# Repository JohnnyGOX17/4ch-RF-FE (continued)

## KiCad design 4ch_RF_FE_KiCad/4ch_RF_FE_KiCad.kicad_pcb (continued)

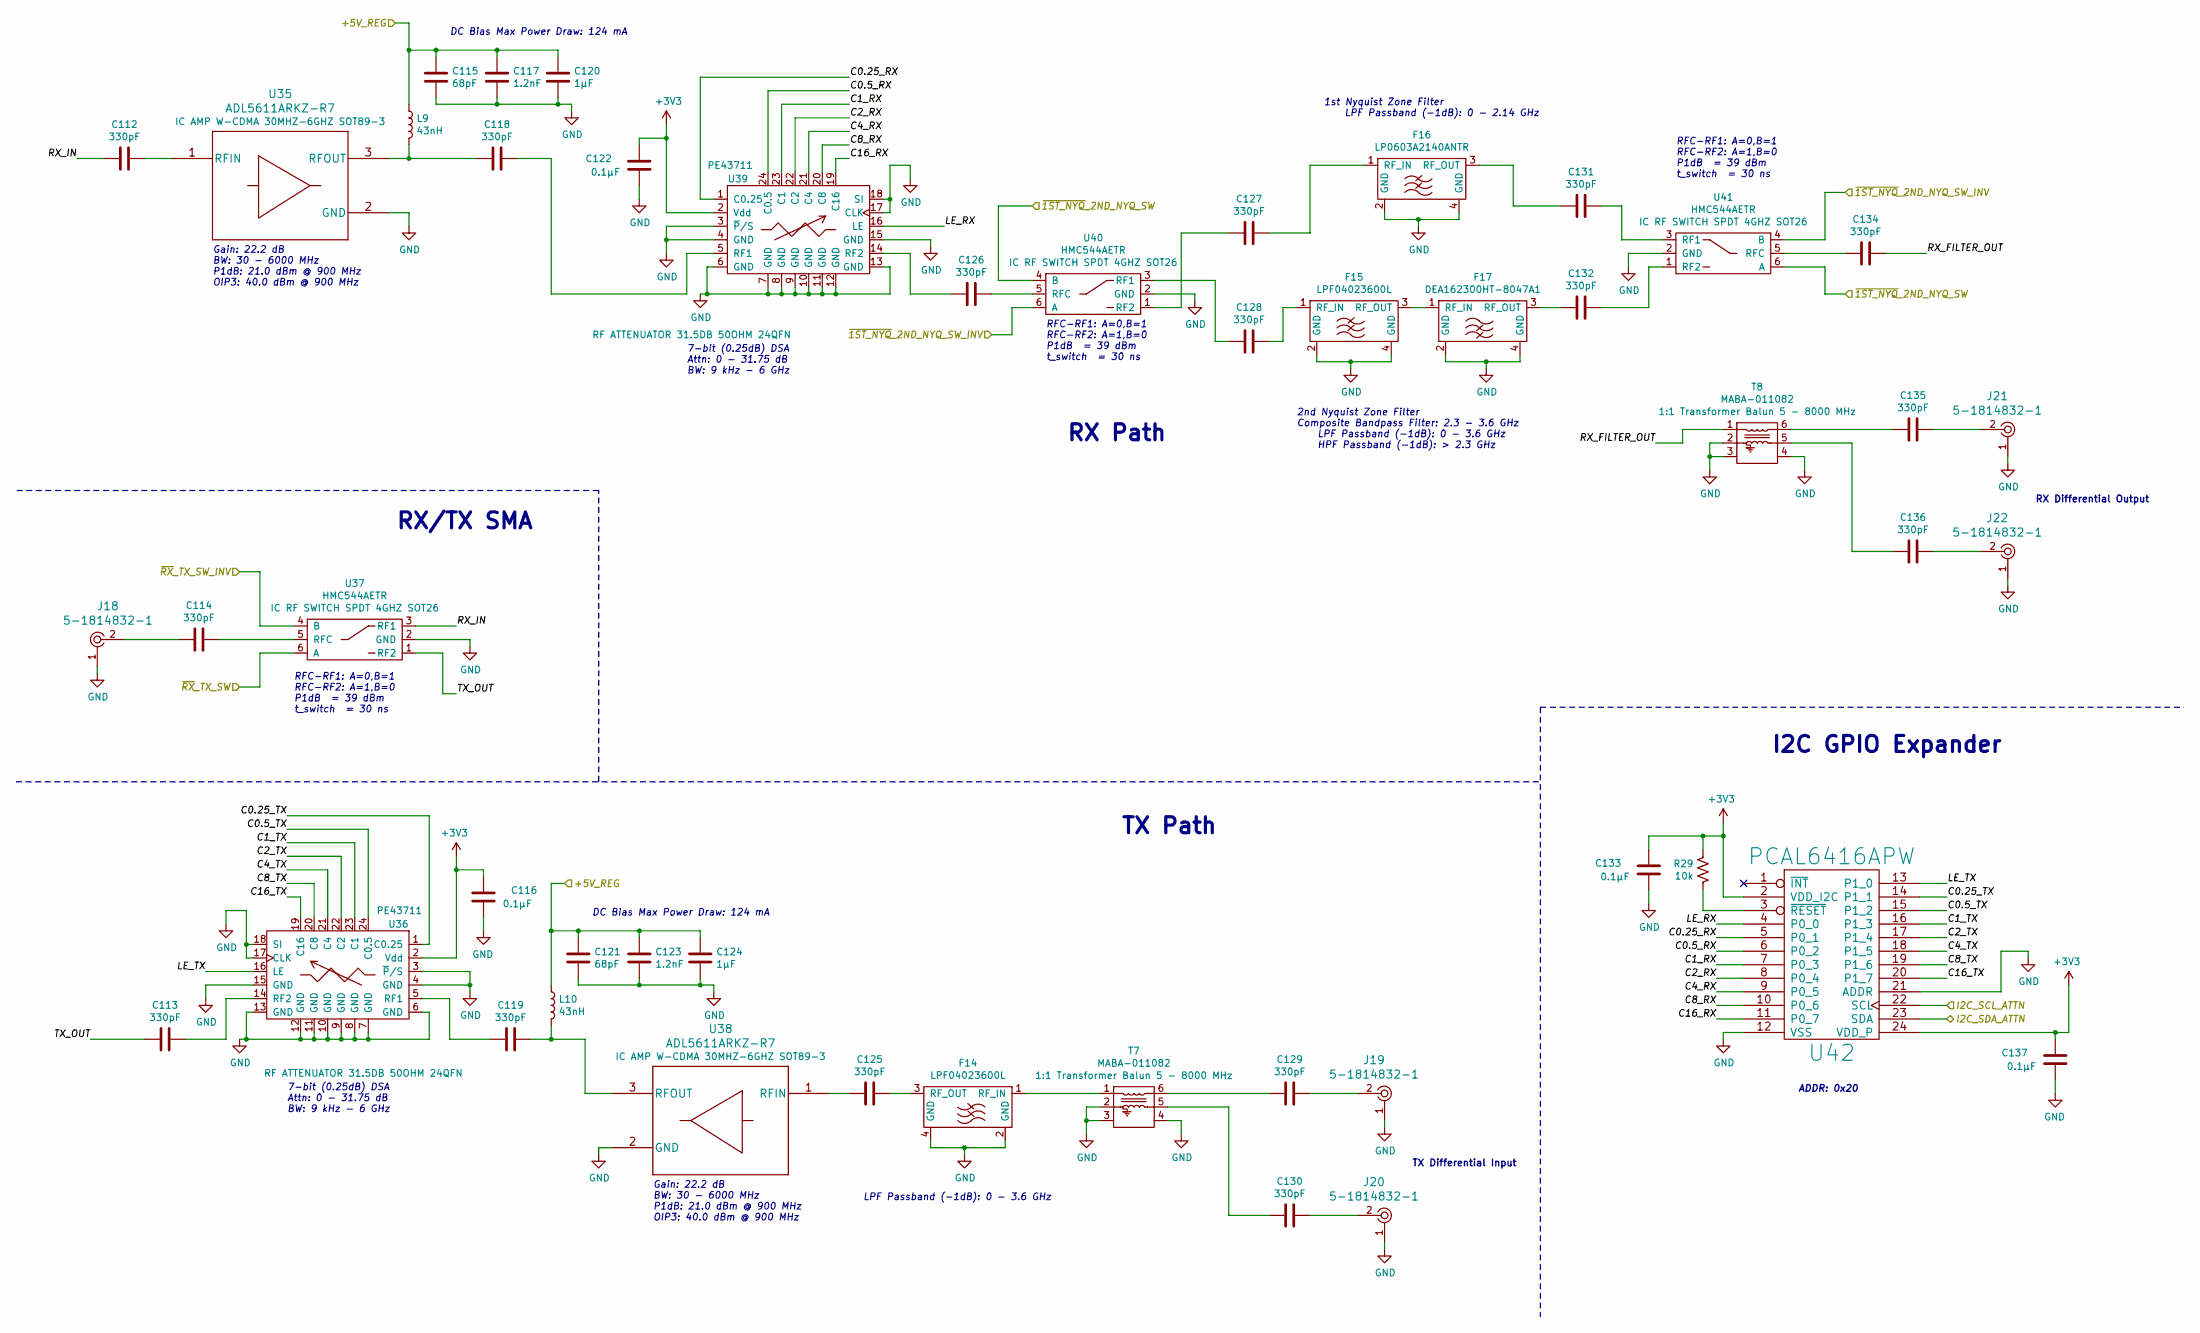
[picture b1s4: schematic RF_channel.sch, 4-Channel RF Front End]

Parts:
C34, C35, C36, C40, C41, C47, C48, C49, C50, C51, C52, C53, C54, C56, C57, C58: 330pF; C_0402_1005Metric; Digi-Key PN 399-7787-1-ND
C37, C43: 68pF; C_0402_1005Metric; Digi-Key PN 399-19382-1-ND
C38, C44, C55, C59: 0.1µF; C_0402_1005Metric; Digi-Key PN 490-13342-1-ND
C39, C45: 1.2nF; C_0603_1608Metric_Pad1.05x0.95mm_HandSolder; Digi-Key PN 399-7851-1-ND
C42, C46: 1µF; C_0603_1608Metric_Pad1.05x0.95mm_HandSolder; Digi-Key PN 1276-1942-1-ND
F2, F3: LPF04023600L; F_0402_1005Metric_2x2_LGA; Digi-Key PN 1284-1984-1-ND
F4: LP0603A2140ANTR; F_0603_2x2_LGA; Digi-Key PN 478-2914-1-ND
F5: DEA162300HT-8047A1; F_DEA16_LGA; Digi-Key PN 445-175383-1-ND
J3, J4, J5, J6, J7: 5-1814832-1; RF_SMA_Vertical_5-1814832-1; MPN 5-1814832-1; Digi-Key_PN A97594-ND
L3, L4: 43nH; L_0603_1608Metric_Pad1.05x0.95mm_HandSolder; Digi-Key PN 490-6892-1-ND
R29: 10k; R_0402_1005Metric; Digi-Key PN 311-10.0KLRCT-ND
T1, T2: MABA-011082; T_6pin_23_balun; Digi-Key PN 1465-1843-1-ND
U11, U14: ADL5611ARKZ-R7; Digi-Key PN ADL5611ARKZ-R7CT-ND
U12, U15: PE43711; QFN-24-1EP_4x4mm_P0.5mm_EP2.7x2.7mm; Digi-Key PN 1046-1138-1-ND
U13, U16, U17: HMC544AETR; SOT-23-6_Handsoldering; Digi-Key PN 1127-1856-1-ND
U18: PCAL6416APW; TSSOP-24_W4.40mm; Digi-Key PN 568-9922-1-ND

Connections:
+3V3: C38.1, C44.1, C55.1, C59.1, R29.1, U12.2 (Vdd), U15.2 (Vdd), U18.2 (VDD_I2C), U18.24 (VDD_P); also elsewhere on the board
/Digitial I/O via PMOD/~RX~_TX_SW0_INV: U13.4 (B); also elsewhere on the board
/Power Input & Regulation/+5V_CH0: C37.1, C39.1, C42.1, C43.1, C45.1, C46.1, L3.1, L4.1; also elsewhere on the board
/RF_ch0/C0.5_RX: U15.24 (C0.5), U18.6 (P0_2)
/RF_ch0/C0.5_TX: U12.24 (C0.5), U18.15 (P1_2)
/RF_ch0/C0.25_RX: U15.1 (C0.25), U18.5 (P0_1)
/RF_ch0/C0.25_TX: U12.1 (C0.25), U18.14 (P1_1)
/RF_ch0/C1_RX: U15.23 (C1), U18.7 (P0_3)
/RF_ch0/C1_TX: U12.23 (C1), U18.16 (P1_3)
/RF_ch0/C2_RX: U15.22 (C2), U18.8 (P0_4)
/RF_ch0/C2_TX: U12.22 (C2), U18.17 (P1_4)
/RF_ch0/C4_RX: U15.21 (C4), U18.9 (P0_5)
/RF_ch0/C4_TX: U12.21 (C4), U18.18 (P1_5)
/RF_ch0/C8_RX: U15.20 (C8), U18.10 (P0_6)
/RF_ch0/C8_TX: U12.20 (C8), U18.19 (P1_6)
/RF_ch0/C16_RX: U15.19 (C16), U18.11 (P0_7)
/RF_ch0/C16_TX: U12.19 (C16), U18.20 (P1_7)
/RF_ch0/I2C_SCL_ATTN: U18.22 (SCL); also elsewhere on the board
/RF_ch0/I2C_SDA_ATTN: U18.23 (SDA); also elsewhere on the board
/RF_ch0/LE_RX: U15.16 (LE), U18.4 (P0_0)
/RF_ch0/LE_TX: U12.16 (LE), U18.13 (P1_0)
/RF_ch0/RX_FILTER_OUT: C56.1, T2.1
/RF_ch0/RX_IN: C34.2, U13.3 (RF1)
/RF_ch0/TX_OUT: C35.2, U13.1 (RF2)
/RF_ch0/~1ST_NYQ~_2ND_NYQ_SW: U16.4 (B), U17.6 (A); also elsewhere on the board
/RF_ch0/~1ST_NYQ~_2ND_NYQ_SW_INV: U16.6 (A), U17.4 (B); also elsewhere on the board
/RF_ch0/~RX~_TX_SW: U13.6 (A); also elsewhere on the board
GND: C37.2, C38.2, C39.2, C42.2, C43.2, C44.2, C45.2, C46.2, C55.2, C59.2, F2.2 (GND), F2.4 (GND), F3.2 (GND), F3.4 (GND), F4.2 (GND), F4.4 (GND), F5.2 (GND), F5.4 (GND), J3.1, J4.1, J5.1, J6.1, J7.1, T1.2, T1.3, T1.4, T2.2, T2.3, T2.4, U11.2 (GND), U12.3 (~P~/S), U12.4 (GND), U12.6 (GND), U12.7 (GND), U12.8 (GND), U12.9 (GND), U12.10 (GND), U12.11 (GND), U12.12 (GND), U12.13 (GND), U12.15 (GND), U12.17 (CLK), U12.18 (SI), U13.2 (GND), U14.2 (GND), U15.3 (~P~/S), U15.4 (GND), U15.6 (GND), U15.7 (GND), U15.8 (GND), U15.9 (GND), U15.10 (GND), U15.11 (GND), U15.12 (GND), U15.13 (GND), U15.15 (GND), U15.17 (CLK), U15.18 (SI), U16.2 (GND), U17.2 (GND), U18.12 (VSS), U18.21 (ADDR); also elsewhere on the board
unnamed: C34.1, U11.1 (RFIN)
unnamed: C35.1, U12.14 (RF2)
unnamed: C36.1, U13.5 (RFC)
unnamed: C36.2, J3.2
unnamed: C40.1, U15.5 (RF1)
unnamed: C40.2, L3.2, U11.3 (RFOUT)
unnamed: C41.1, L4.2, U14.3 (RFOUT)
unnamed: C41.2, U12.5 (RF1)
unnamed: C47.1, F2.3 (RF_OUT)
unnamed: C47.2, U14.1 (RFIN)
unnamed: C48.1, U16.5 (RFC)
unnamed: C48.2, U15.14 (RF2)
unnamed: C49.1, F4.1 (RF_IN)
unnamed: C49.2, U16.1 (RF2)
unnamed: C50.1, F3.1 (RF_IN)
unnamed: C50.2, U16.3 (RF1)
unnamed: C51.1, J4.2
unnamed: C51.2, T1.6
unnamed: C52.1, J5.2
unnamed: C52.2, T1.5
unnamed: C53.1, U17.3 (RF1)
unnamed: C53.2, F4.3 (RF_OUT)
unnamed: C54.1, U17.1 (RF2)
unnamed: C54.2, F5.3 (RF_OUT)
unnamed: C56.2, U17.5 (RFC)
unnamed: C57.1, J6.2
unnamed: C57.2, T2.6
unnamed: C58.1, J7.2
unnamed: C58.2, T2.5
unnamed: F2.1 (RF_IN), T1.1
unnamed: F3.3 (RF_OUT), F5.1 (RF_IN)

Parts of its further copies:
C60, C61, C62, C66, C67, C73, C74, C75, C76, C77, C78, C79, C80, C82, C83, C84, C86, C87, C88, C92, C93, C99, C100, C101, C102, C103, C104, C105, C106, C108, C109, C110, C112, C113, C114, C118, C119, C125, C126, C127, C128, C129, C130, C131, C132, C134, C135, C136: 330pF; C_0402_1005Metric; Digi-Key PN 399-7787-1-ND
C63, C69, C89, C95, C115, C121: 68pF; C_0402_1005Metric; Digi-Key PN 399-19382-1-ND
C64, C70, C81, C85, C90, C96, C107, C111, C116, C122, C133, C137: 0.1µF; C_0402_1005Metric; Digi-Key PN 490-13342-1-ND
C65, C71, C91, C97, C117, C123: 1.2nF; C_0603_1608Metric_Pad1.05x0.95mm_HandSolder; Digi-Key PN 399-7851-1-ND
C68, C72, C94, C98, C120, C124: 1µF; C_0603_1608Metric_Pad1.05x0.95mm_HandSolder; Digi-Key PN 1276-1942-1-ND
F6, F7, F10, F11, F14, F15: LPF04023600L; F_0402_1005Metric_2x2_LGA; Digi-Key PN 1284-1984-1-ND
F8, F12, F16: LP0603A2140ANTR; F_0603_2x2_LGA; Digi-Key PN 478-2914-1-ND
F9, F13, F17: DEA162300HT-8047A1; F_DEA16_LGA; Digi-Key PN 445-175383-1-ND
J8, J9, J10, J11, J12, J13, J14, J15, J16, J17, J18, J19, J20, J21, J22: 5-1814832-1; RF_SMA_Vertical_5-1814832-1; MPN 5-1814832-1; Digi-Key_PN A97594-ND
L5, L6, L7, L8, L9, L10: 43nH; L_0603_1608Metric_Pad1.05x0.95mm_HandSolder; Digi-Key PN 490-6892-1-ND
R26, R27, R28: 10k; R_0402_1005Metric; Digi-Key PN 311-10.0KLRCT-ND
T3, T4, T5, T6, T7, T8: MABA-011082; T_6pin_23_balun; Digi-Key PN 1465-1843-1-ND
U20, U23, U28, U31, U36, U39: PE43711; QFN-24-1EP_4x4mm_P0.5mm_EP2.7x2.7mm; Digi-Key PN 1046-1138-1-ND
U21, U24, U25, U29, U32, U33, U37, U40, U41: HMC544AETR; SOT-23-6_Handsoldering; Digi-Key PN 1127-1856-1-ND
U26, U34, U42: PCAL6416APW; TSSOP-24_W4.40mm; Digi-Key PN 568-9922-1-ND

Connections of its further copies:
+3V3: C64.1, C70.1, C81.1, C85.1, C90.1, C96.1, C107.1, C111.1, C116.1, C122.1, C133.1, C137.1, R26.1, R27.1, R28.1, U20.2 (Vdd), U23.2 (Vdd), U26.2 (VDD_I2C), U26.24 (VDD_P), U28.2 (Vdd), U31.2 (Vdd), U34.2 (VDD_I2C), U34.24 (VDD_P), U36.2 (Vdd), U39.2 (Vdd), U42.2 (VDD_I2C), U42.24 (VDD_P); also elsewhere on the board
/Digitial I/O via PMOD/~RX~_TX_SW1_INV: U21.4 (B); also elsewhere on the board
/Digitial I/O via PMOD/~RX~_TX_SW2_INV: U37.4 (B); also elsewhere on the board
/Digitial I/O via PMOD/~RX~_TX_SW3_INV: U29.4 (B); also elsewhere on the board
/Power Input & Regulation/+5V_CH1: C63.1, C65.1, C68.1, C69.1, C71.1, C72.1, L5.1, L6.1; also elsewhere on the board
/Power Input & Regulation/+5V_CH2: C115.1, C117.1, C120.1, C121.1, C123.1, C124.1, L9.1, L10.1; also elsewhere on the board
/Power Input & Regulation/+5V_CH3: C89.1, C91.1, C94.1, C95.1, C97.1, C98.1, L7.1, L8.1; also elsewhere on the board
/RF_ch0/~1ST_NYQ~_2ND_NYQ_SW: U24.4 (B), U25.6 (A), U32.4 (B), U33.6 (A), U40.4 (B), U41.6 (A); also elsewhere on the board
/RF_ch0/~1ST_NYQ~_2ND_NYQ_SW_INV: U24.6 (A), U25.4 (B), U32.6 (A), U33.4 (B), U40.6 (A), U41.4 (B); also elsewhere on the board
/RF_ch1/C0.5_RX: U23.24 (C0.5), U26.6 (P0_2)
/RF_ch1/C0.5_TX: U20.24 (C0.5), U26.15 (P1_2)
/RF_ch1/C0.25_RX: U23.1 (C0.25), U26.5 (P0_1)
/RF_ch1/C0.25_TX: U20.1 (C0.25), U26.14 (P1_1)
/RF_ch1/C1_RX: U23.23 (C1), U26.7 (P0_3)
/RF_ch1/C1_TX: U20.23 (C1), U26.16 (P1_3)
/RF_ch1/C2_RX: U23.22 (C2), U26.8 (P0_4)
/RF_ch1/C2_TX: U20.22 (C2), U26.17 (P1_4)
/RF_ch1/C4_RX: U23.21 (C4), U26.9 (P0_5)
/RF_ch1/C4_TX: U20.21 (C4), U26.18 (P1_5)
/RF_ch1/C8_RX: U23.20 (C8), U26.10 (P0_6)
/RF_ch1/C8_TX: U20.20 (C8), U26.19 (P1_6)
/RF_ch1/C16_RX: U23.19 (C16), U26.11 (P0_7)
/RF_ch1/C16_TX: U20.19 (C16), U26.20 (P1_7)
/RF_ch1/I2C_SCL_ATTN: U26.22 (SCL); also elsewhere on the board
/RF_ch1/I2C_SDA_ATTN: U26.23 (SDA); also elsewhere on the board
/RF_ch1/LE_RX: U23.16 (LE), U26.4 (P0_0)
/RF_ch1/LE_TX: U20.16 (LE), U26.13 (P1_0)
/RF_ch1/RX_FILTER_OUT: C82.1, T4.1
/RF_ch1/RX_IN: C60.2, U21.3 (RF1)
/RF_ch1/TX_OUT: C61.2, U21.1 (RF2)
/RF_ch1/~RX~_TX_SW: U21.6 (A); also elsewhere on the board
/RF_ch2/C0.5_RX: U39.24 (C0.5), U42.6 (P0_2)
/RF_ch2/C0.5_TX: U36.24 (C0.5), U42.15 (P1_2)
/RF_ch2/C0.25_RX: U39.1 (C0.25), U42.5 (P0_1)
/RF_ch2/C0.25_TX: U36.1 (C0.25), U42.14 (P1_1)
/RF_ch2/C1_RX: U39.23 (C1), U42.7 (P0_3)
/RF_ch2/C1_TX: U36.23 (C1), U42.16 (P1_3)
/RF_ch2/C2_RX: U39.22 (C2), U42.8 (P0_4)
/RF_ch2/C2_TX: U36.22 (C2), U42.17 (P1_4)
/RF_ch2/C4_RX: U39.21 (C4), U42.9 (P0_5)
/RF_ch2/C4_TX: U36.21 (C4), U42.18 (P1_5)
/RF_ch2/C8_RX: U39.20 (C8), U42.10 (P0_6)
/RF_ch2/C8_TX: U36.20 (C8), U42.19 (P1_6)
/RF_ch2/C16_RX: U39.19 (C16), U42.11 (P0_7)
/RF_ch2/C16_TX: U36.19 (C16), U42.20 (P1_7)
/RF_ch2/I2C_SCL_ATTN: U42.22 (SCL); also elsewhere on the board
/RF_ch2/I2C_SDA_ATTN: U42.23 (SDA); also elsewhere on the board
/RF_ch2/LE_RX: U39.16 (LE), U42.4 (P0_0)
/RF_ch2/LE_TX: U36.16 (LE), U42.13 (P1_0)
/RF_ch2/RX_FILTER_OUT: C134.1, T8.1
/RF_ch2/RX_IN: C112.2, U37.3 (RF1)
/RF_ch2/TX_OUT: C113.2, U37.1 (RF2)
/RF_ch2/~RX~_TX_SW: U37.6 (A); also elsewhere on the board
/RF_ch3/C0.5_RX: U31.24 (C0.5), U34.6 (P0_2)
/RF_ch3/C0.5_TX: U28.24 (C0.5), U34.15 (P1_2)
/RF_ch3/C0.25_RX: U31.1 (C0.25), U34.5 (P0_1)
/RF_ch3/C0.25_TX: U28.1 (C0.25), U34.14 (P1_1)
/RF_ch3/C1_RX: U31.23 (C1), U34.7 (P0_3)
/RF_ch3/C1_TX: U28.23 (C1), U34.16 (P1_3)
/RF_ch3/C2_RX: U31.22 (C2), U34.8 (P0_4)
/RF_ch3/C2_TX: U28.22 (C2), U34.17 (P1_4)
/RF_ch3/C4_RX: U31.21 (C4), U34.9 (P0_5)
/RF_ch3/C4_TX: U28.21 (C4), U34.18 (P1_5)
/RF_ch3/C8_RX: U31.20 (C8), U34.10 (P0_6)
/RF_ch3/C8_TX: U28.20 (C8), U34.19 (P1_6)
/RF_ch3/C16_RX: U31.19 (C16), U34.11 (P0_7)
/RF_ch3/C16_TX: U28.19 (C16), U34.20 (P1_7)
/RF_ch3/I2C_SCL_ATTN: U34.22 (SCL); also elsewhere on the board
/RF_ch3/I2C_SDA_ATTN: U34.23 (SDA); also elsewhere on the board
/RF_ch3/LE_RX: U31.16 (LE), U34.4 (P0_0)
/RF_ch3/LE_TX: U28.16 (LE), U34.13 (P1_0)
/RF_ch3/RX_FILTER_OUT: C108.1, T6.1
/RF_ch3/RX_IN: C86.2, U29.3 (RF1)
/RF_ch3/TX_OUT: C87.2, U29.1 (RF2)
/RF_ch3/~RX~_TX_SW: U29.6 (A); also elsewhere on the board
GND: C63.2, C64.2, C65.2, C68.2, C69.2, C70.2, C71.2, C72.2, C81.2, C85.2, C89.2, C90.2, C91.2, C94.2, C95.2, C96.2, C97.2, C98.2, C107.2, C111.2, C115.2, C116.2, C117.2, C120.2, C121.2, C122.2, C123.2, C124.2, C133.2, C137.2, F6.2 (GND), F6.4 (GND), F7.2 (GND), F7.4 (GND), F8.2 (GND), F8.4 (GND), F9.2 (GND), F9.4 (GND), F10.2 (GND), F10.4 (GND), F11.2 (GND), F11.4 (GND), F12.2 (GND), F12.4 (GND), F13.2 (GND), F13.4 (GND), F14.2 (GND), F14.4 (GND), F15.2 (GND), F15.4 (GND), F16.2 (GND), F16.4 (GND), F17.2 (GND), F17.4 (GND), J8.1, J9.1, J10.1, J11.1, J12.1, J13.1, J14.1, J15.1, J16.1, J17.1, J18.1, J19.1, J20.1, J21.1, J22.1, T3.2, T3.3, T3.4, T4.2, T4.3, T4.4, T5.2, T5.3, T5.4, T6.2, T6.3, T6.4, T7.2, T7.3, T7.4, T8.2, T8.3, T8.4, U20.3 (~P~/S), U20.4 (GND), U20.6 (GND), U20.7 (GND), U20.8 (GND), U20.9 (GND), U20.10 (GND), U20.11 (GND), U20.12 (GND), U20.13 (GND), U20.15 (GND), U20.17 (CLK), U20.18 (SI), U21.2 (GND), U23.3 (~P~/S), U23.4 (GND), U23.6 (GND), U23.7 (GND), U23.8 (GND), U23.9 (GND), U23.10 (GND), U23.11 (GND), U23.12 (GND), U23.13 (GND), U23.15 (GND), U23.17 (CLK), U23.18 (SI), U24.2 (GND), U25.2 (GND), U26.12 (VSS), U26.21 (ADDR), U28.3 (~P~/S), U28.4 (GND), U28.6 (GND), U28.7 (GND), U28.8 (GND), U28.9 (GND), U28.10 (GND), U28.11 (GND), U28.12 (GND), U28.13 (GND), U28.15 (GND), U28.17 (CLK), U28.18 (SI), U29.2 (GND), U31.3 (~P~/S), U31.4 (GND), U31.6 (GND), U31.7 (GND), U31.8 (GND), U31.9 (GND), U31.10 (GND), U31.11 (GND), U31.12 (GND), U31.13 (GND), U31.15 (GND), U31.17 (CLK), U31.18 (SI), U32.2 (GND), U33.2 (GND), U34.12 (VSS), U34.21 (ADDR), U36.3 (~P~/S), U36.4 (GND), U36.6 (GND), U36.7 (GND), U36.8 (GND), U36.9 (GND), U36.10 (GND), U36.11 (GND), U36.12 (GND), U36.13 (GND), U36.15 (GND), U36.17 (CLK), U36.18 (SI), U37.2 (GND), U39.3 (~P~/S), U39.4 (GND), U39.6 (GND), U39.7 (GND), U39.8 (GND), U39.9 (GND), U39.10 (GND), U39.11 (GND), U39.12 (GND), U39.13 (GND), U39.15 (GND), U39.17 (CLK), U39.18 (SI), U40.2 (GND), U41.2 (GND), U42.12 (VSS), U42.21 (ADDR); also elsewhere on the board
unnamed 162: C60.1; also elsewhere on the board
unnamed: C61.1, U20.14 (RF2)
unnamed: C62.1, U21.5 (RFC)
unnamed: C62.2, J8.2
unnamed: C66.1, U23.5 (RF1)
unnamed 167: C66.2, L5.2; also elsewhere on the board
unnamed 168: C67.1, L6.2; also elsewhere on the board
unnamed: C67.2, U20.5 (RF1)
unnamed: C73.1, F6.3 (RF_OUT)
unnamed 171: C73.2; also elsewhere on the board
unnamed: C74.1, U24.5 (RFC)
unnamed: C74.2, U23.14 (RF2)
unnamed: C75.1, F8.1 (RF_IN)
unnamed: C75.2, U24.1 (RF2)
unnamed: C76.1, F7.1 (RF_IN)
unnamed: C76.2, U24.3 (RF1)
unnamed: C77.1, J9.2
unnamed: C77.2, T3.6
unnamed: C78.1, J10.2
unnamed: C78.2, T3.5
unnamed: C79.1, U25.3 (RF1)
unnamed: C79.2, F8.3 (RF_OUT)
unnamed: C80.1, U25.1 (RF2)
unnamed: C80.2, F9.3 (RF_OUT)
unnamed: C82.2, U25.5 (RFC)
unnamed: C83.1, J11.2
unnamed: C83.2, T4.6
unnamed: C84.1, J12.2
unnamed: C84.2, T4.5
unnamed 191: C86.1; also elsewhere on the board
unnamed: C87.1, U28.14 (RF2)
unnamed: C88.1, U29.5 (RFC)
unnamed: C88.2, J13.2
unnamed: C92.1, U31.5 (RF1)
unnamed 196: C92.2, L7.2; also elsewhere on the board
unnamed 197: C93.1, L8.2; also elsewhere on the board
unnamed: C93.2, U28.5 (RF1)
unnamed: C99.1, F10.3 (RF_OUT)
unnamed 200: C99.2; also elsewhere on the board
unnamed: C100.1, U32.5 (RFC)
unnamed: C100.2, U31.14 (RF2)
unnamed: C101.1, F12.1 (RF_IN)
unnamed: C101.2, U32.1 (RF2)
unnamed: C102.1, F11.1 (RF_IN)
unnamed: C102.2, U32.3 (RF1)
unnamed: C103.1, J14.2
unnamed: C103.2, T5.6
unnamed: C104.1, J15.2
unnamed: C104.2, T5.5
unnamed: C105.1, U33.3 (RF1)
unnamed: C105.2, F12.3 (RF_OUT)
unnamed: C106.1, U33.1 (RF2)
unnamed: C106.2, F13.3 (RF_OUT)
unnamed: C108.2, U33.5 (RFC)
unnamed: C109.1, J16.2
unnamed: C109.2, T6.6
unnamed: C110.1, J17.2
unnamed: C110.2, T6.5
unnamed 220: C112.1; also elsewhere on the board
unnamed: C113.1, U36.14 (RF2)
unnamed: C114.1, U37.5 (RFC)
unnamed: C114.2, J18.2
unnamed: C118.1, U39.5 (RF1)
unnamed 225: C118.2, L9.2; also elsewhere on the board
unnamed 226: C119.1, L10.2; also elsewhere on the board
unnamed: C119.2, U36.5 (RF1)
unnamed: C125.1, F14.3 (RF_OUT)
unnamed 229: C125.2; also elsewhere on the board
unnamed: C126.1, U40.5 (RFC)
unnamed: C126.2, U39.14 (RF2)
unnamed: C127.1, F16.1 (RF_IN)
unnamed: C127.2, U40.1 (RF2)
unnamed: C128.1, F15.1 (RF_IN)
unnamed: C128.2, U40.3 (RF1)
unnamed: C129.1, J19.2
unnamed: C129.2, T7.6
unnamed: C130.1, J20.2
unnamed: C130.2, T7.5
unnamed: C131.1, U41.3 (RF1)
unnamed: C131.2, F16.3 (RF_OUT)
unnamed: C132.1, U41.1 (RF2)
unnamed: C132.2, F17.3 (RF_OUT)
unnamed: C134.2, U41.5 (RFC)
unnamed: C135.1, J21.2
unnamed: C135.2, T8.6
unnamed: C136.1, J22.2
unnamed: C136.2, T8.5
unnamed: F6.1 (RF_IN), T3.1
unnamed: F7.3 (RF_OUT), F9.1 (RF_IN)
unnamed: F10.1 (RF_IN), T5.1
unnamed: F11.3 (RF_OUT), F13.1 (RF_IN)
unnamed: F14.1 (RF_IN), T7.1
unnamed: F15.3 (RF_OUT), F17.1 (RF_IN)
unnamed: R27.2, U26.3 (~RESET)
unnamed: R28.2, U34.3 (~RESET)

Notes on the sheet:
TX Path
TX Differential Input
LPF Passband (-1dB): 0 - 3.6 GHz
Gain: 22.2 dB BW: 30 - 6000 MHz P1dB: 21.0 dBm @ 900 MHz OIP3: 40.0 dBm @ 900 MHz
DC Bias Max Power Draw: 124 mA
RFC-RF1: A=0,B=1 RFC-RF2: A=1,B=0 P1dB = 39 dBm t_switch = 30 ns
ADDR: 0x20
2nd Nyquist Zone Filter Composite Bandpass Filter: 2.3 - 3.6 GHz LPF Passband (-1dB): 0 - 3.6 GHz HPF Passband (-1dB): > 2.3 GHz
1st Nyquist Zone Filter LPF Passband (-1dB): 0 - 2.14 GHz
RX Differential Output
RX Path
RX/TX SMA
I2C GPIO Expander
7-bit (0.25dB) DSA Attn: 0 - 31.75 dB BW: 9 kHz - 6 GHz

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
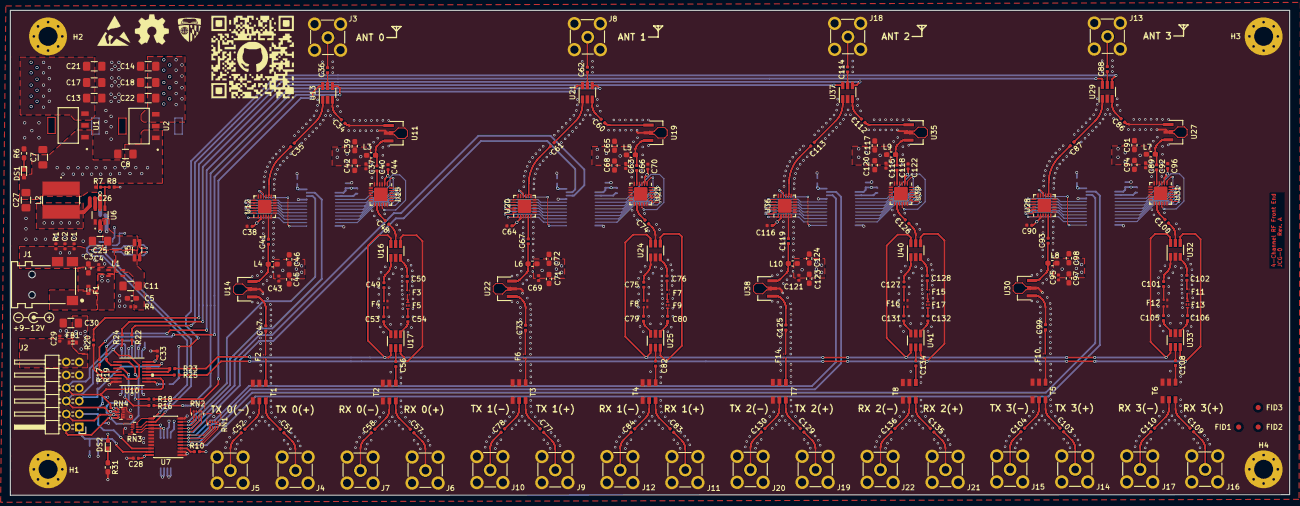
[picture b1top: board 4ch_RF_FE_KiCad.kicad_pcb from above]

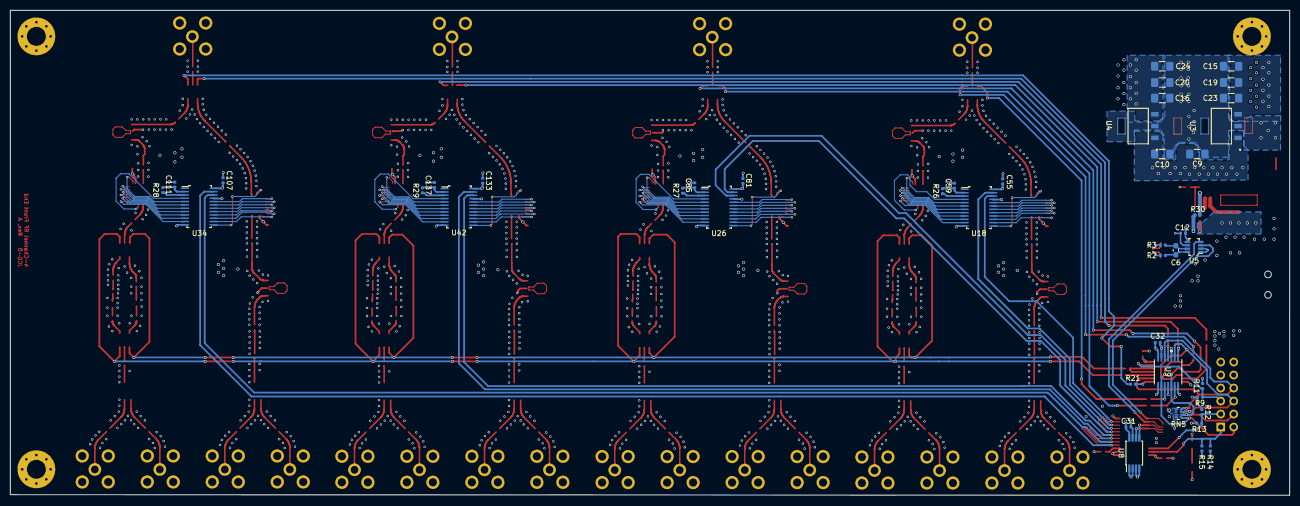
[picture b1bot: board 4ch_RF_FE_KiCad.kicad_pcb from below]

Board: 4 copper layers, 249.9 x 94.7 mm, 282 parts (44 on the bottom side), 267 nets.

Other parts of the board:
U19, U22, U27, U30, U35, U38: RK_3; ADL5611ARKZ-R7

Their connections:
GND: U19.2, U22.2, U27.2, U30.2, U35.2, U38.2; also elsewhere on the board
unnamed 162: U19.1; also elsewhere on the board
unnamed 167: U19.3; also elsewhere on the board
unnamed 168: U22.3; also elsewhere on the board
unnamed 171: U22.1; also elsewhere on the board
unnamed 191: U27.1; also elsewhere on the board
unnamed 196: U27.3; also elsewhere on the board
unnamed 197: U30.3; also elsewhere on the board
unnamed 200: U30.1; also elsewhere on the board
unnamed 220: U35.1; also elsewhere on the board
unnamed 225: U35.3; also elsewhere on the board
unnamed 226: U38.3; also elsewhere on the board
unnamed 229: U38.1; also elsewhere on the board

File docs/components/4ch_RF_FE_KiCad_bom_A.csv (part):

Component,Description,Part,References,Value,Footprint,Quantity Per PCB,Datasheet,Digi-Key PN,Category,DK_Datasheet_Link,DK_Detail_Page,Family,MPN,Manufacturer,Status
1,Unpolarized capacitor,C,C1 C4 C12 C26 C28 C29 C31 C32 C33 C38 C44 C55 C59 C64 C70 C81 C85 C90 C96 C107 C111 C116 C122 C133 C137,0.1µF,C_0402_1005Metric,25,https://search.murata.co.jp/Ceramy/image/img/A01X/G101/ENG/G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,490-13342-1-ND,,,,,,,
2,Unpolarized capacitor,C,C39 C45 C65 C71 C91 C97 C117 C123,1.2nF,C_0603_1608Metric_Pad1.05x0.95mm_HandSolder,8,https://api.kemet.com/component-edge/download/datasheet/C060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,399-7851-1-ND,,,,,,,
3,Unpolarized capacitor,C,C7 C8 C9 C10 C11 C13 C14 C15 C16 C17 C18 C19 C20 C21 C22 C23 C24 C25 C30,10µF,C_1206_3216Metric_Pad1.42x1.75mm_HandSolder,19,http://www.samsungsem.com/kr/support/product-search/mlcc/CL3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,1276-1804-1-ND,,,,,,,
4,Unpolarized capacitor,C,C3 C5 C6 C42 C46 C68 C72 C94 C98 C120 C124,1µF,C_0603_1608Metric_Pad1.05x0.95mm_HandSolder,11,http://www.samsungsem.com/kr/support/product-search/mlcc/CL1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,1276-1942-1-ND,,,,,,,
5,Unpolarized capacitor,C,C27,22µF,C_1206_3216Metric_Pad1.42x1.75mm_HandSolder,1,http://www.samsungsem.com/kr/support/product-search/mlcc/CL3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,1276-3146-1-ND,,,,,,,
6,Unpolarized capacitor,C,C34 C35 C36 C40 C41 C47 C48 C49 C50 C51 C52 C53 C54 C56 C57 C58 C60 C61 C62 C66 C67 C73 C74 C75 C76 C77 C78 C79 C80 C82 C83 C84 C86 C87 C88 C92 C93 C99 C100 C101 C102 C103 C104 C105 C106 C108 C109 C110 C112 C113 C114 C118 C119 C125 C126 C127 C128 C129 C130 C131 C132 C134 C135 C136,330pF,C_0402_1005Metric,64,https://api.kemet.com/component-edge/download/datasheet/C040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,399-7787-1-ND,,,,,,,
7,Unpolarized capacitor,C,C37 C43 C63 C69 C89 C95 C115 C121,68pF,C_0402_1005Metric,8,https://api.kemet.com/component-edge/download/datasheet/C040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,399-19382-1-ND,,,,,,,
8,LED GREEN CLEAR CHIP SMD,LTST-C190KGKT,DS1 DS2,LTST-C190KGKT,LED_0603,2,http://optoelectronics.liteon.com/upload/download/DS22-2000-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,160-1435-1-ND,Optoelectronics,http://optoelectronics.liteon.com/upload/download/DS22-2000-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,/product-detail/en/lite-on-inc/LTST-C190KGKT/160-1435-1-ND/386814,LED Indication - Discrete,LTST-C190KGKT,Lite-On Inc.,Active
9,RF FILTER HIGH PASS 2.4GHZ 0603,DEA162300HT-8047A1,F5 F9 F13 F17,DEA162300HT-8047A1,F_DEA16_LGA,4,https://media.digikey.com/pdf/Data%20Sheets/TDK%20PDFs/DEA16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,445-175383-1-ND,,,,,,TDK,
10,FUSE BOARD MOUNT 5A 32VDC 0603,ERB-RE5R00V,F1,ERB-RE5R00V,603,1,https://industrial.panasonic.com/cdbs/www-data/pdf/AFA0000/A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,P15125CT-ND,Circuit Protection,,,Fuses,,Panasonic,Active
11,DC to 2.14 GHz 50 Ohm Low Pass Filter,LP0603A2140ANTR,F4 F8 F12 F16,LP0603A2140ANTR,F_0603_2x2_LGA,4,http://datasheets.avx.com/lp0603.pdf,478-2914-1-ND,,,,,,AVX,
12,DC to 3600 MHz 50 Ohm Low Pass Filter,LPF04023600L,F2 F3 F6 F7 F10 F11 F14 F15,LPF04023600L,F_0402_1005Metric_2x2_LGA,8,https://media.digikey.com/pdf/Data%20Sheets/American%20Techn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,1284-1984-1-ND,,,,,,ATC,
13,FERRITE BEAD 1.5 KOHM 0603 1LN,BLM18HE152SN1D,FB1,BLM18HE152SN1D,603,1,https://www.murata.com/en-us/products/productdata/8796741599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,490-5216-1-ND,Filters,https://www.murata.com/en-us/products/productdata/8796741599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,/product-detail/en/murata-electronics-north-america/BLM18HE152SN1D/490-5216-1-ND/1948392,Ferrite Beads and Chips,BLM18HE152SN1D,Murata Electronics North America,Active
14,CONN SMA JACK STR 50 OHM PCB,5-1814832-1,J3 J4 J5 J6 J7 J8 J9 J10 J11 J12 J13 J14 J15 J16 J17 J18 J19 J20 J21 J22,5-1814832-1,RF_SMA_Vertical_5-1814832-1,20,https://www.te.com/commerce/DocumentDelivery/DDEController?A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,A97594-ND,"Connectors, Interconnects",https://www.te.com/commerce/DocumentDelivery/DDEController?A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,/product-detail/en/te-connectivity-amp-connectors/5-1814832-1/A97594-ND/1755982,Coaxial Connectors (RF),5-1814832-1,TE Connectivity AMP Connectors,Active
15,CONN PWR JACK 1.75X4.75MM SOLDER,PJ1-021-SMT-TR,J1,PJ1-021-SMT-TR,CUI_PJ1-021-SMT-TR,1,https://www.cuidevices.com/product/resource/pj1-021-smt-tr.pdf,CP1-021PJCT-ND,,,,,,,
16,CONN HDR 12POS 0.1 TIN PCB R/A,PPTC062LJBN-RC,J2,PPTC062LJBN-RC,PinHeader_2x06_P2.54mm_Horizontal,1,https://media.digikey.com/pdf/Data%20Sheets/Sullins%20PDFs/F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,S5520-ND,"Connectors, Interconnects",,,"Rectangular Connectors - Headers, Female Pins",,Sullins Connector Solutions,Active
17,Inductor,L,L3 L4 L5 L6 L7 L8 L9 L10,43nH,L_0603_1608Metric_Pad1.05x0.95mm_HandSolder,8,https://search.murata.co.jp/Ceramy/image/img/P02/JELF243A-0024.pdf,490-6892-1-ND,,,,,,,
18,CMC 500 Ohms @ 100MHz 2A DCR 40 mOhm,ACP3225,L1,ACP3225,CMC_3225_2x2_LGA,1,https://product.tdk.com/info/en/catalog/datasheets/cmf_comme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,445-172408-1-ND,,,,,,,
19,FIXED IND 3.3UH 3.5A 20 MOHM SMD,SRR6038-3R3Y,L2,SRR6038-3R3Y,SRR6038-3R3Y,1,https://www.bourns.com/docs/Product-Datasheets/SRR6038.pdf,SRR6038-3R3YCT-ND,,,,,,,
20,"Resistor, US symbol",R_US,R2 R3,10,R_0402_1005Metric,2,https://www.yageo.com/upload/media/product/productsearch/dat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,311-10.0LRCT-ND,,,,,,,
21,"Resistor, US symbol",R_US,R23 R25,100,R_0402_1005Metric,2,https://www.yageo.com/upload/media/product/productsearch/dat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,311-100LRCT-ND,,,,,,,
22,"Resistor, US symbol",R_US,R4,100k,R_0402_1005Metric,1,https://www.yageo.com/upload/media/product/productsearch/dat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,311-100KLRCT-ND,,,,,,,
23,"Resistor, US symbol",R_US,R8 R10 R11 R12 R14 R26 R27 R28 R29 R30,10k,R_0402_1005Metric,10,https://www.yageo.com/upload/media/product/productsearch/dat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,311-10.0KLRCT-ND,,,,,,,
24,"Resistor, US symbol",R_US,R6,180,R_0603_1608Metric_Pad1.05x0.95mm_HandSolder,1,https://www.yageo.com/upload/media/product/productsearch/dat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,311-180GRCT-ND,,,,,,,
25,"Resistor, US symbol",R_US,R16 R17 R18 R19 R20 R21 R22 R24,33,R_0402_1005Metric,8,https://www.yageo.com/upload/media/product/productsearch/dat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,311-33.0LRCT-ND,,,,,,,
26,"Resistor, US symbol",R_US,R7,61.9k,R_0402_1005Metric,1,https://www.yageo.com/upload/media/product/productsearch/dat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,311-61.9KLRCT-ND,,,,,,,
27,"Resistor, US symbol",R_US,R31,75,R_0603_1608Metric_Pad1.05x0.95mm_HandSolder,1,https://www.yageo.com/upload/media/product/productsearch/dat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,311-75.0HRCT-ND,,,,,,,
28,RES 0.002 OHM 1% 1W 1206,CSR1206-0R002F1,R5,CSR1206-0R002F1,CSR_4pin_1206_3216Metric_Pad1.42x1.75mm_HandSolder,1,https://riedon.com/media/pdf/CSR.pdf,696-1370-1-ND,,,,,,,
29,"4 resistor network, parallel topology, DIP package",R_Pack04,RN1 RN2 RN3 RN4,EXB-28V103JX,R_Array_Convex_4x0402,4,https://industrial.panasonic.com/cdbs/www-data/pdf/AOC0000/A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,Y7103CT-ND,,,,,,,
30,1:1 Transformer Balun 5 - 8000 MHz,MABA-011082,T1 T2 T3 T4 T5 T6 T7 T8,MABA-011082,T_6pin_23_balun,8,https://cdn.macom.com/datasheets/MABA-011082.pdf,1465-1843-1-ND,,,,,,,
31,IC AMP W-CDMA 30MHZ-6GHZ SOT89-3,ADL5611ARKZ-R7,U11 U14 U19 U22 U27 U30 U35 U38,ADL5611ARKZ-R7,ADL5611ARKZ-R7,8,https://www.analog.com/media/en/technical-documentation/data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,ADL5611ARKZ-R7CT-ND,,,,,,,
32,IC RF SWITCH SPDT 4GHZ SOT26,HMC544AETR,U13 U16 U17 U21 U24 U25 U29 U32 U33 U37 U40 U41,HMC544AETR,SOT-23-6_Handsoldering,12,https://www.analog.com/media/en/technical-documentation/data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,1127-1856-1-ND,,,,,,,
33,IC CURRENT MONITOR 1% SOT23-8,INA219AIDCNR,U5,INA219AIDCNR,SOT-23-8,1,http://www.ti.com/general/docs/suppproductinfo.tsp?distId=10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,296-23770-1-ND,Integrated Circuits (ICs),http://www.ti.com/general/docs/suppproductinfo.tsp?distId=10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,/product-detail/en/texas-instruments/INA219AIDCNR/296-23770-1-ND/1952550,PMIC - Current Regulation/Management,INA219AIDCNR,Texas Instruments,Active
34,"2Kb (256x8) I2C Serial EEPROM, 1.6-5.5V, TSSOP-8",M24C02-FDW,U8,M24C02-FDW,TSSOP-8_4.4x3mm_P0.65mm,1,http://www.st.com/content/ccc/resource/technical/document/da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,497-15746-1-ND,,,,,,,
35,IC REG LINEAR 5V 300MA SOT223-3,MCP1755ST-5002E_DB,U1 U2 U3 U4,MCP1755ST-5002E_DB,MCP1755ST-5002E_DB,4,http://www.microchip.com/mymicrochip/filehandler.aspx?ddocna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,MCP1755ST-5002E/DBCT-ND,,,,,,,
36,"Low voltage 8-channel I2C switch with reset, TSSOP-24",PCA9548APW,U7,PCA9548APW,TSSOP-24_4.4x7.8mm_P0.65mm,1,http://www.ti.com/lit/ds/symlink/pca9548a.pdf,296-21775-1-ND,,,,,,,
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
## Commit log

2020-03-03 (+) docs & KiCad design
2020-03-08 initial completion of schematic capture
2020-03-11 (+) starting layout
2020-03-11 change footprint/schematic paths from absolute -> relative
2020-03-14 (+) power & DIO layout & impedance calcs
2020-03-17 RF layout
2020-03-19 more optimized RF layout, smaller overal layout
2020-03-20 final layout
2020-03-20 (+) final silkscreen changes
2020-03-20 (+) schematic output
2020-03-21 (+) QR code -> shipped to OSH Park
2020-04-02 bom tool
2020-04-07 (+) BOM CXV
2020-04-16 (+) Device tree bindings for digital components
2020-04-16 (+) pic to README
2020-04-16 INA219 DNP in device tree
2020-04-16 fixed syntax error in DT
2020-05-02 (+) shottky diode for testing
2020-05-07 (+) I2C setup/control script for Raspberry Pi's
2020-12-18 additions to README
